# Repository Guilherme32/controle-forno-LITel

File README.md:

# Controle do forno do LITel

Último teste realizado (14/10/2022)

Esse repositório guarda o que foi desenvolvido para o controle do forno do
Laboratório de Instrumentação e Telemetria da UFJF (LITel)

# Informações

O sistema funciona aplicando um controle por lógica Fuzzy (FLC), com modulação
de potência por detecção de zero, para manter a temperatura vista pelo sensor
central do forno no valor especificado. Também pode funcionar por potência fixa.

> Este README contém algumas informações básicas do controlador, e uma
explicação das interfaces de comunicação. *Assim, possui o necessário para
utilizar o projeto*. Maiores detalhes do funcionamento de outras partes podem
ser encontradas no **manual.md** e também na documentação dos códigos.

Para interação com o usuário existem duas interfaces de comunicação:
- WiFi
- Serial

# Comunicação WiFi

Para se comunicar com o controlador por wifi, basta estar na mesma rede. Para
isso, deve-se conectar no ponto de acesso do esp ou estar na rede em que ele
estiver conectado.

Uma vez conectado à mesma rede do esp, o programa pode ser controlado através
das páginas acessíveis em **http://\<endereço ip\>** ou  **\<endereço ip\>:80**.
O endereço depende de qual interface wifi está sendo utilizada.

## Ponto de Acesso (Access Point)

O esp está configurado para funcionar em modo "access point", permitindo que
dispositivos se conectem a ele. As credenciais de acesso são:

> SSID: forno-litel
>
> Senha: 787Cu7kg

Nesse modo, o programa pode ser acessado pelo ip:

> ip: 192.168.4.1

## Modo Estação (station)

Nesse modo, o esp tentará se conectar à rede que estiver configurado para se
conectar. A única forma de alterar essa configuração é pelas próprias páginas
web.

> Ao mudar a configuração, ele automaticamente irá se desconectar da rede em
que estava anteriormente. Logo a forma mais indicada de fazer essa alteração é
acessando através do ponto de acesso.

O ip quando nesse modo depende do roteador (ou ponto de acesso no geral) em que
está se conectando. Esse ip será informado na página de conexão e também pode
ser descoberto pelo comando serial **!netinfo**.

## Páginas

### Página Principal

A página principal serve apenas como uma entrada à interface. Ela permite acesso
às outras páginas do sistema, e também linka para esse repositório.

> Todas as outras páginas possuem também links para as outras páginas do sistema
e para esse repositório.

### Conexão

Essa página mostra as informações de conexão (SSID, senha, ip), e permite mudar
as credenciais da rede a ser acessada pelo modo estação.

> No caso do modo estação, a página também indica se o esp está devidamente
conectado

### Controle

Essa é a página mais importante, e também a mais pesada. É normal que ela demore
muitos segundos para carregar.

> Se a página estiver apresentando instabilidades, por favor reporte para mim ou
crie um "issue" aqui no repositório

A página possui alguns componentes:

- Operação: 
    O forno pode funcionar por potência fixa ou por set point. Uma vez que
    o modo é selecionado, e o valor desejado inserido na caixa de texto, o botão
    enviar pode ser pressionado para enviar as informações para o
    microcontrolador.

- Informações instantâneas:
    Para melhor entendimento, algumas informações são colocadas referentes ao
    funcionamento do forno no último instante recebido.
    - A potência enviada às resistências;
    - Se o sistema está em regime transitório ou alcançou o estacionário;
    - A temperatura no sensor principal (S5, o que fica no centro).

- Gráfico:
    Um gráfico temporal com os valores de set point (se estiver no modo de
    controle) e os valores lidos por todos os sensores. Cada conjunto pode ser
    apagado ou redesenhado para maior clareza. Também, vale notar que o gráfico
    somente mostra as últimas 240 amostras.

> O gráfico e as informações instantâneas são atualizados com 5 segundos. Dessa
forma, o gráfico mostra amostras dos últimos 20 minutos.

# Comunicação Serial

A interface serial funciona utilizando uma taxa (baud rate) de **115200 bits/
s**, com 8 bits de dados e 1 de parada (stop bit).

A comunicação ocorre através de comandos. Para enviar um comando, deve-se enviar
primeiro um caracter de início (!), então escrever o comando, seguido pelo
argumento, caso exista, seguindo a formatação exigida.

Os comandos implementados são:
- **!netinfo**: Devolve as informações de rede:
    - SSID, senha e ip do modo ap;
    - Se estiver devidamente conectado no modo sta, SSID e IP desse modo;
    - Se não estiver, indica que o sta está desconectado;

- **!tempX**, onde X é o índice do sensor: Devolve a temperatura lida no sensor
de índice X;

- **!sensorX**, onde X é o índice do sensor: Parecido com o **temp**, mas
retorna o inteiro entre 0 e 1023 que representa a leitura crua do adc (analog -
digital converter) do esp;

- **!settXXX.X**, onde XXX.X é a temperatura em ºC, com três dígitos antes
da vírgula, e um depois: Seta o set point do sistema de controle para o valor
de temperatura passado. Para não alcançar a temperatura máxima de operação do
sensor, o valor máximo que pode ser passado é 140ºC. Automaticamente ativa o
modo de controle;

- **!setpXXX**, onde XXX é um inteiro representando a quantidade de semiciclos
ligados: Seta a relação de potência a ser enviada para as resistências. O
período da modulação de potência é de 120 semiciclos, logo o valor enviado deve
estar entre 0 e 120 (inclusivo), onde 0 é carga desligada e 120 é carga em plena
potência. Automaticamente ativa o modo de potência fixa;

> A formatação dos argumentos deve ser exatamente como descrita, ou o programa
pode não responder adequadamente

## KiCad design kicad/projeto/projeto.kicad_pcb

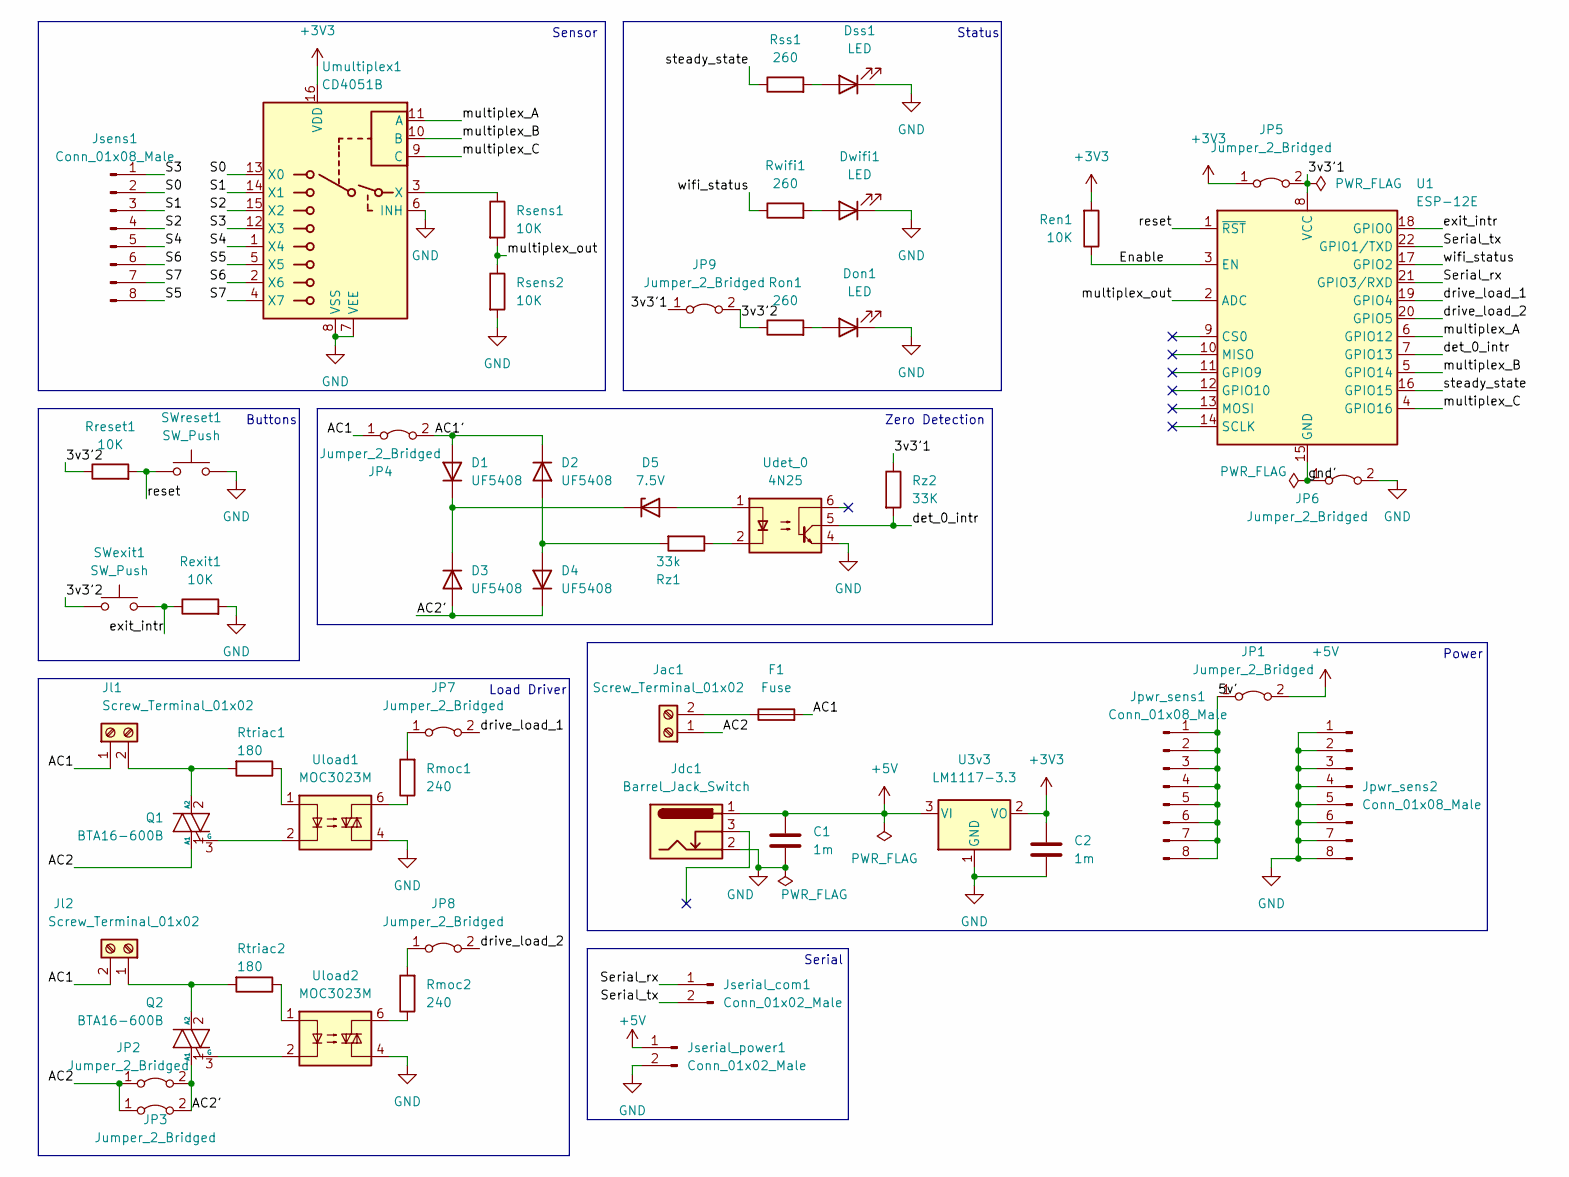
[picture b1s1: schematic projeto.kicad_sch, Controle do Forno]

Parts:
C1, C2: 1m; C_Radial_D10.0mm_H16.0mm_P5.00mm
D1, D2, D3, D4: UF5408; D_T-1_P5.08mm_Horizontal
D5: 7.5V; D_T-1_P5.08mm_Horizontal
Don1: LED; LED_D3.0mm
Dss1: LED; LED_D3.0mm
Dwifi1: LED; LED_D3.0mm
F1: Fuse; Fuseholder_Cylinder-5x20mm_Stelvio-Kontek_PTF78_Horizontal_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
JP1, JP2, JP3, JP4, JP5, JP6, JP8, JP9: Jumper_2_Bridged; jumper_10mm
JP7: Jumper_2_Bridged
Jac1: Screw_Terminal_01x02; TerminalBlock_bornier-2_P5.08mm
Jdc1: Barrel_Jack_Switch; BarrelJack_CUI_PJ-102AH_Horizontal
Jl1, Jl2: Screw_Terminal_01x02; TerminalBlock_bornier-2_P5.08mm
Jpwr_sens1, Jpwr_sens2: Conn_01x08_Male; PinHeader_1x08_P2.54mm_Vertical
Jsens1: Conn_01x08_Male; PinHeader_1x08_P2.54mm_Vertical
Jserial_com1: Conn_01x02_Male; PinHeader_1x02_P2.54mm_Vertical
Jserial_power1: Conn_01x02_Male; PinHeader_1x02_P2.54mm_Vertical
Q1, Q2: BTA16-600B; TO-220-3_Vertical
Ren1: 10K; R_Axial_DIN0207_L6.3mm_D2.5mm_P7.62mm_Horizontal
Rexit1: 10K; R_Axial_DIN0207_L6.3mm_D2.5mm_P7.62mm_Horizontal
Rmoc1, Rmoc2: 240; R_Axial_DIN0207_L6.3mm_D2.5mm_P7.62mm_Horizontal
Ron1: 260; R_Axial_DIN0207_L6.3mm_D2.5mm_P7.62mm_Horizontal
Rreset1: 10K; R_Axial_DIN0207_L6.3mm_D2.5mm_P7.62mm_Horizontal
Rsens1, Rsens2: 10K; R_Axial_DIN0207_L6.3mm_D2.5mm_P7.62mm_Horizontal
Rss1: 260; R_Axial_DIN0207_L6.3mm_D2.5mm_P7.62mm_Horizontal
Rtriac1, Rtriac2: 180; R_Axial_DIN0309_L9.0mm_D3.2mm_P12.70mm_Horizontal
Rwifi1: 260; R_Axial_DIN0207_L6.3mm_D2.5mm_P7.62mm_Horizontal
Rz1: 33k; R_Axial_DIN0309_L9.0mm_D3.2mm_P12.70mm_Horizontal
Rz2: 33K; R_Axial_DIN0207_L6.3mm_D2.5mm_P7.62mm_Horizontal
SWexit1: SW_Push; SW_PUSH_6mm
SWreset1: SW_Push; SW_PUSH_6mm
U1: ESP-12E
U3v3: LM1117-3.3; TO-220-3_Vertical
Udet_0: 4N25; DIP-6_W7.62mm_Socket_LongPads
Uload1, Uload2: MOC3023M; DIP-6_W7.62mm_Socket_LongPads
Umultiplex1: CD4051B; DIP-16_W7.62mm_Socket

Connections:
+3V3: C2.1, JP5.1 (A), Ren1.2, U3v3.2 (VO), Umultiplex1.16 (VDD)
+5V: C1.1, JP1.2 (B), Jdc1.1, Jserial_power1.1, U3v3.3 (VI)
/3v3'1: JP5.2 (B), JP9.1 (A), Rz2.1, U1.8 (VCC)
/3v3'2: JP9.2 (B), Ron1.1, Rreset1.1, SWexit1.1
/5v': JP1.1 (A), Jpwr_sens1.1, Jpwr_sens1.2, Jpwr_sens1.3, Jpwr_sens1.4, Jpwr_sens1.5, Jpwr_sens1.6, Jpwr_sens1.7, Jpwr_sens1.8
/AC1: F1.2, JP4.1 (A), Jl1.1, Jl2.2
/AC1': D1.2 (A), D2.1 (K), JP4.2 (B)
/AC2: JP2.1 (A), JP3.1 (A), Jac1.1, Q1.1 (A1)
/AC2': D3.2 (A), D4.1 (K), JP2.2 (B), JP3.2 (B), Q2.1 (A1)
/Enable: Ren1.1, U1.3 (EN)
/S0: Jsens1.2, Umultiplex1.13 (X0)
/S1: Jsens1.3, Umultiplex1.14 (X1)
/S2: Jsens1.4, Umultiplex1.15 (X2)
/S3: Jsens1.1, Umultiplex1.12 (X3)
/S4: Jsens1.5, Umultiplex1.1 (X4)
/S5: Jsens1.8, Umultiplex1.5 (X5)
/S6: Jsens1.6, Umultiplex1.2 (X6)
/S7: Jsens1.7, Umultiplex1.4 (X7)
/Serial_rx: Jserial_com1.1, U1.21 (GPIO3/RXD)
/Serial_tx: Jserial_com1.2, U1.22 (GPIO1/TXD)
/det_0_intr: Rz2.2, U1.7 (GPIO13), Udet_0.5
/drive_load_1: JP7.2 (B), U1.19 (GPIO4)
/drive_load_2: JP8.2 (B), U1.20 (GPIO5)
/exit_intr: Rexit1.1, SWexit1.2, U1.18 (GPIO0)
/gnd': JP6.1 (A), U1.15 (GND)
/multiplex_A: U1.6 (GPIO12), Umultiplex1.11 (A)
/multiplex_B: U1.5 (GPIO14), Umultiplex1.10 (B)
/multiplex_C: U1.4 (GPIO16), Umultiplex1.9 (C)
/multiplex_out: Rsens1.2, Rsens2.1, U1.2 (ADC)
/reset: Rreset1.2, SWreset1.1, U1.1 (~RST)
/steady_state: Rss1.1, U1.16 (GPIO15)
/wifi_status: Rwifi1.1, U1.17 (GPIO2)
GND: C1.2, C2.2, Don1.1 (K), Dss1.1 (K), Dwifi1.1 (K), JP6.2 (B), Jdc1.2, Jpwr_sens2.1, Jpwr_sens2.2, Jpwr_sens2.3, Jpwr_sens2.4, Jpwr_sens2.5, Jpwr_sens2.6, Jpwr_sens2.7, Jpwr_sens2.8, Jserial_power1.2, Rexit1.2, Rsens2.2, SWreset1.2, U3v3.1 (GND), Udet_0.4, Uload1.4, Uload2.4, Umultiplex1.6 (INH), Umultiplex1.7 (VEE), Umultiplex1.8 (VSS)
unnamed: D1.1 (K), D3.1 (K), D5.1 (K)
unnamed: D2.2 (A), D4.2 (A), Rz1.2
unnamed: D5.2 (A), Udet_0.1
unnamed: Don1.2 (A), Ron1.2
unnamed: Dss1.2 (A), Rss1.2
unnamed: Dwifi1.2 (A), Rwifi1.2
unnamed: F1.1, Jac1.2
unnamed: Jl1.2, Q1.2 (A2), Rtriac1.2
unnamed: Jl2.1, Q2.2 (A2), Rtriac2.2
unnamed: Q1.3 (G), Uload1.2
unnamed: Q2.3 (G), Uload2.2
unnamed: Rmoc1.1, Uload1.6
unnamed: JP7.1 (A), Rmoc1.2
unnamed: Rmoc2.1, Uload2.6
unnamed: JP8.1 (A), Rmoc2.2
unnamed: Rsens1.1, Umultiplex1.3 (X)
unnamed: Rtriac1.1, Uload1.1
unnamed: Rtriac2.1, Uload2.1
unnamed: Rz1.1, Udet_0.2

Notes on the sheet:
Status
Power
Serial
Zero Detection
Load Driver
Sensor
Buttons

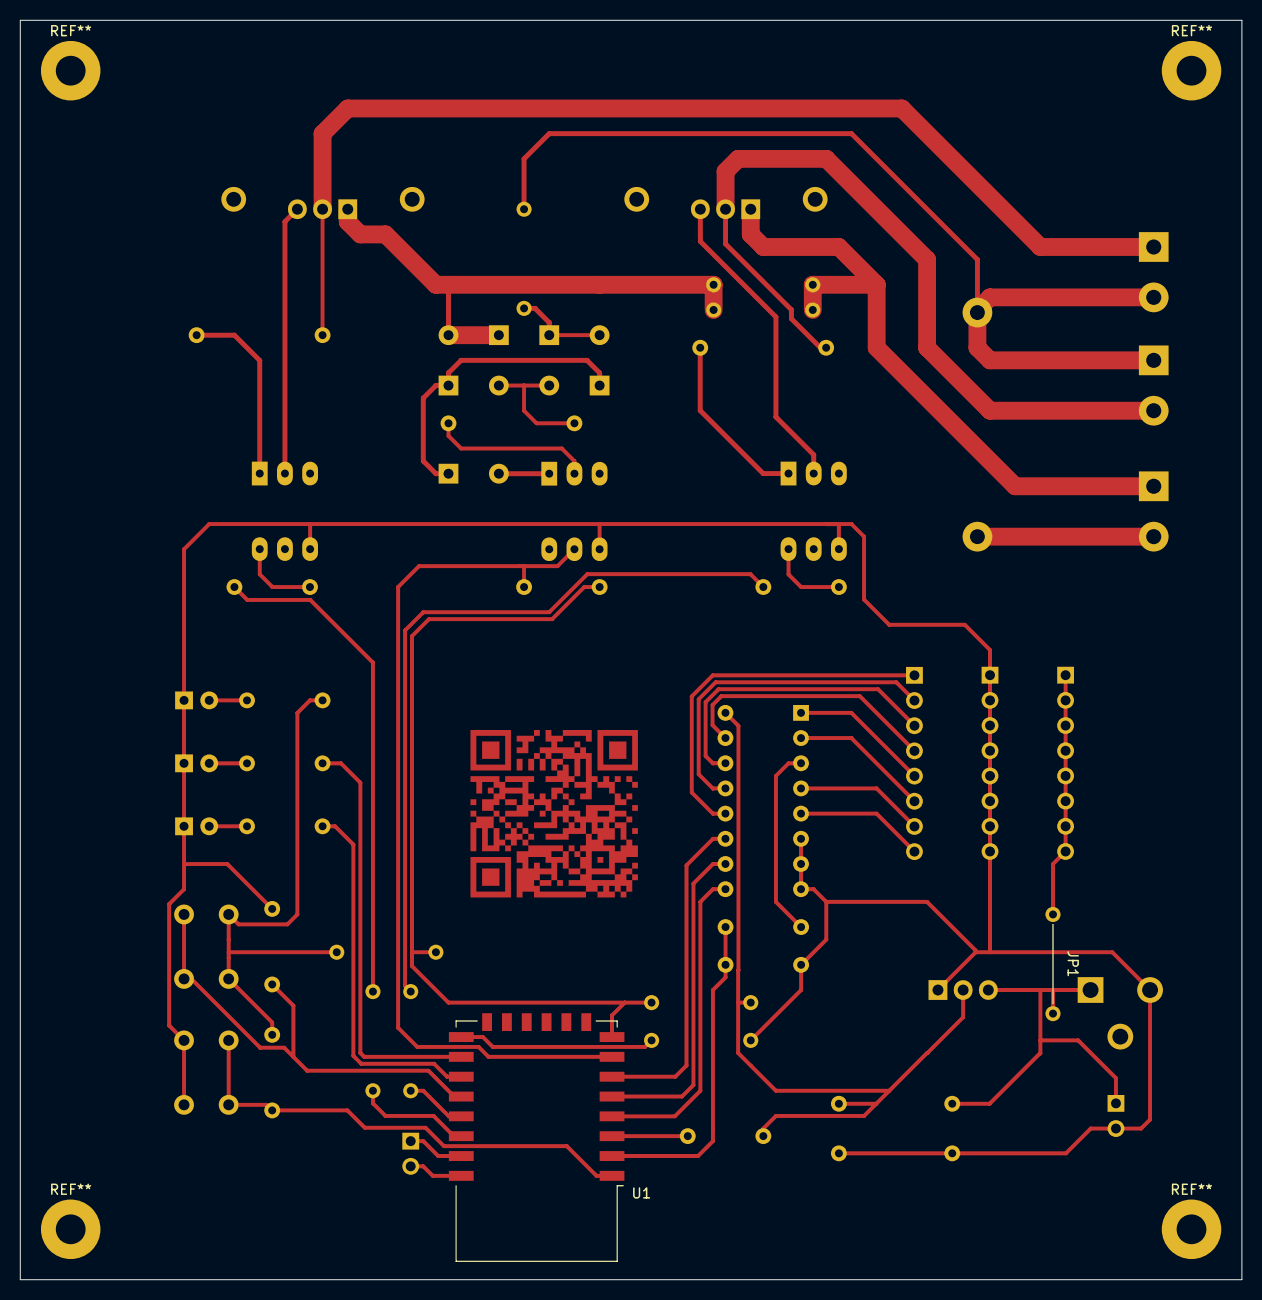
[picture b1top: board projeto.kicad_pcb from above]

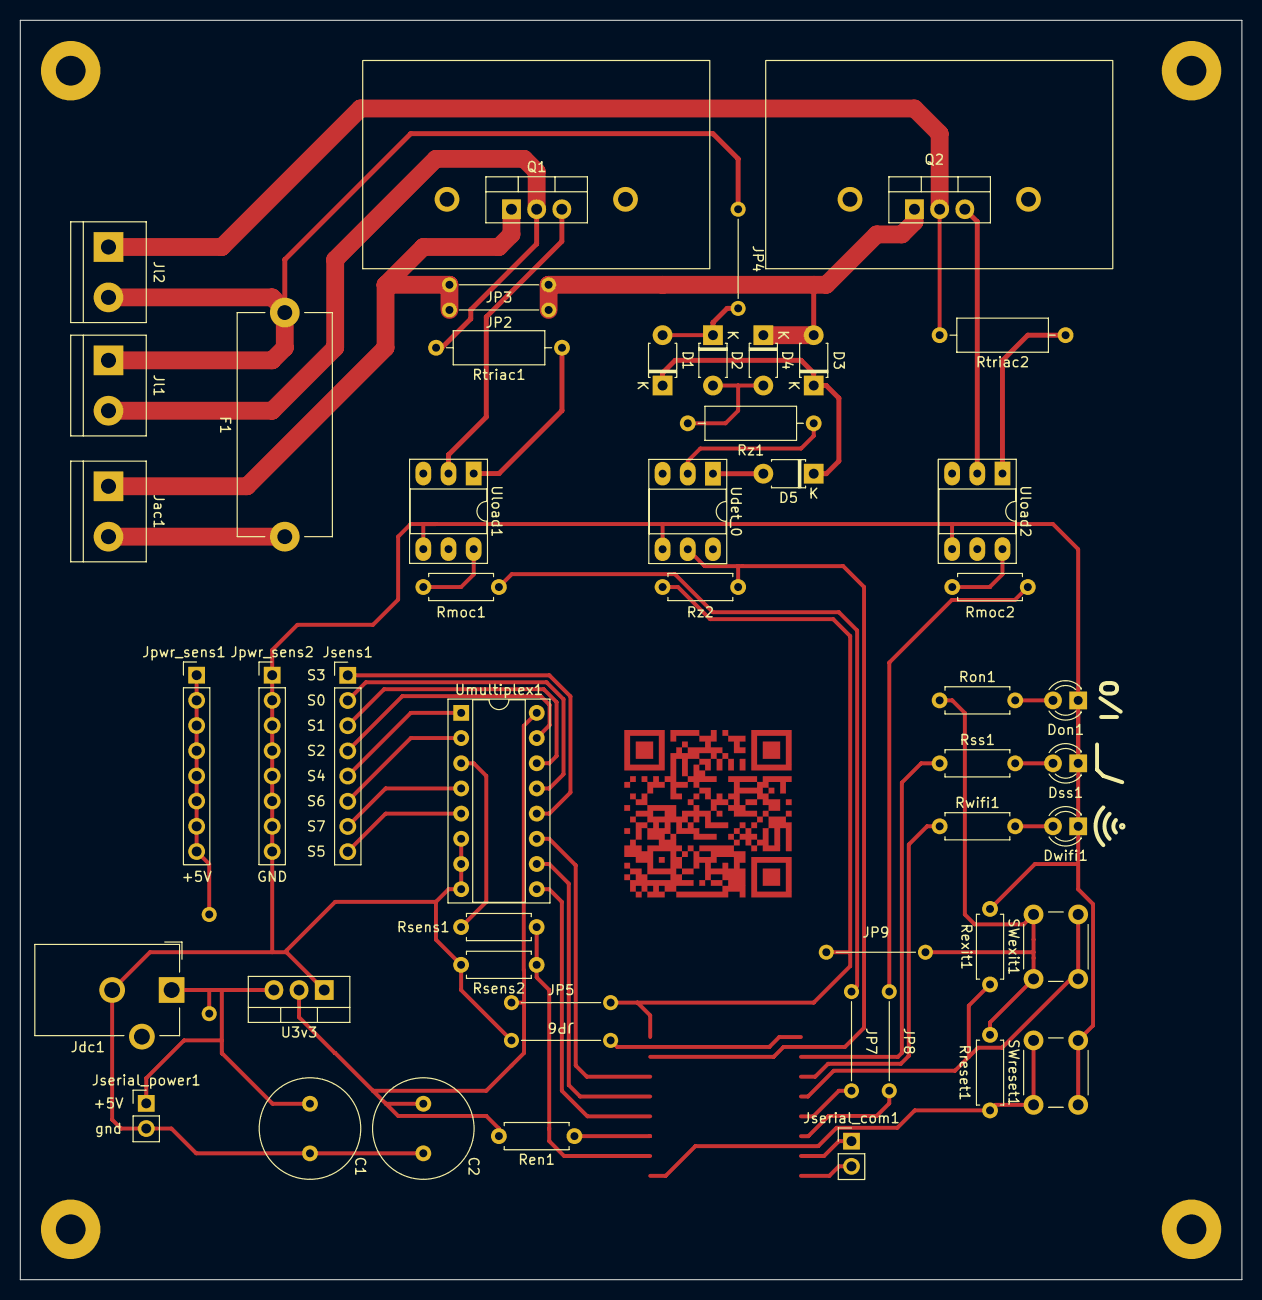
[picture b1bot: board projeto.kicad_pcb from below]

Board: 2 copper layers, 123.2 x 127.0 mm, 53 parts (51 on the bottom side), 52 nets.

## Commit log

2022-06-04 Add comunicação serial
2022-06-04 Add Leitor do sensor
    Ainda sem testar, pq depende do multiplex
2022-06-05 update todo
2022-06-06 add docs
2022-06-06 Add gerenciador de rede
2022-06-08 Remove TODO
    Testei, funcionou :)
2022-06-08 Att serial comm
2022-06-08 Arrumar formula
2022-06-08 Add controller.py
2022-06-08 Add comandos
2022-06-08 Add mais comandos
2022-06-09 Bug fix
2022-06-09 Add inicio da parte web
2022-06-10 Add mais da parte web
    Corrigi o que tinha enviado ate o momento. Agora essa parte ja funciona
2022-06-12 Completar pagina de conexao
2022-06-14 Completar pagina e api de conexão
2022-06-14 Remover arquivos sem uso
2022-06-14 Creditos
2022-06-14 Add checagem de estabilidade
2022-06-15 Finalizou a página de controle
2022-06-18 Iniciou o esquemático
2022-06-18 Add led de status de conexao
2022-06-18 Finalizou esquematico
2022-06-21 Correção de erros do ERC
2022-06-22 Att componentes
2022-06-23 Fazendo a PCB (1)
2022-06-24 Fazendo a PCB
2022-06-27 Small fix
2022-06-28 Add qr code
2022-06-28 Add pcb arredondada
2022-06-28 Add alguns dados na pcb
2022-06-28 Add modelo do jumper
2022-06-29 Escrevendo docs
2022-06-29 Documentando
2022-06-29 Fix PCB
2022-07-02 Generalizando
2022-07-02 Renomeações
2022-07-02 Organização
2022-08-25 Increase clock frequency
2022-08-31 Update control algorithm
2022-08-31 Fix some errors
2022-08-31 Add the test
2022-08-31 Add requirements.txt
2022-09-03 Update control
2022-09-03 Update test
2022-10-07 Improving control and tests
2022-10-14 making tests
2022-10-15 update documentation
2022-10-15 Updating docs
2023-04-09 Rewriting system in C
2023-04-09 Removing notebooks
2023-04-20 Updating the documentation
